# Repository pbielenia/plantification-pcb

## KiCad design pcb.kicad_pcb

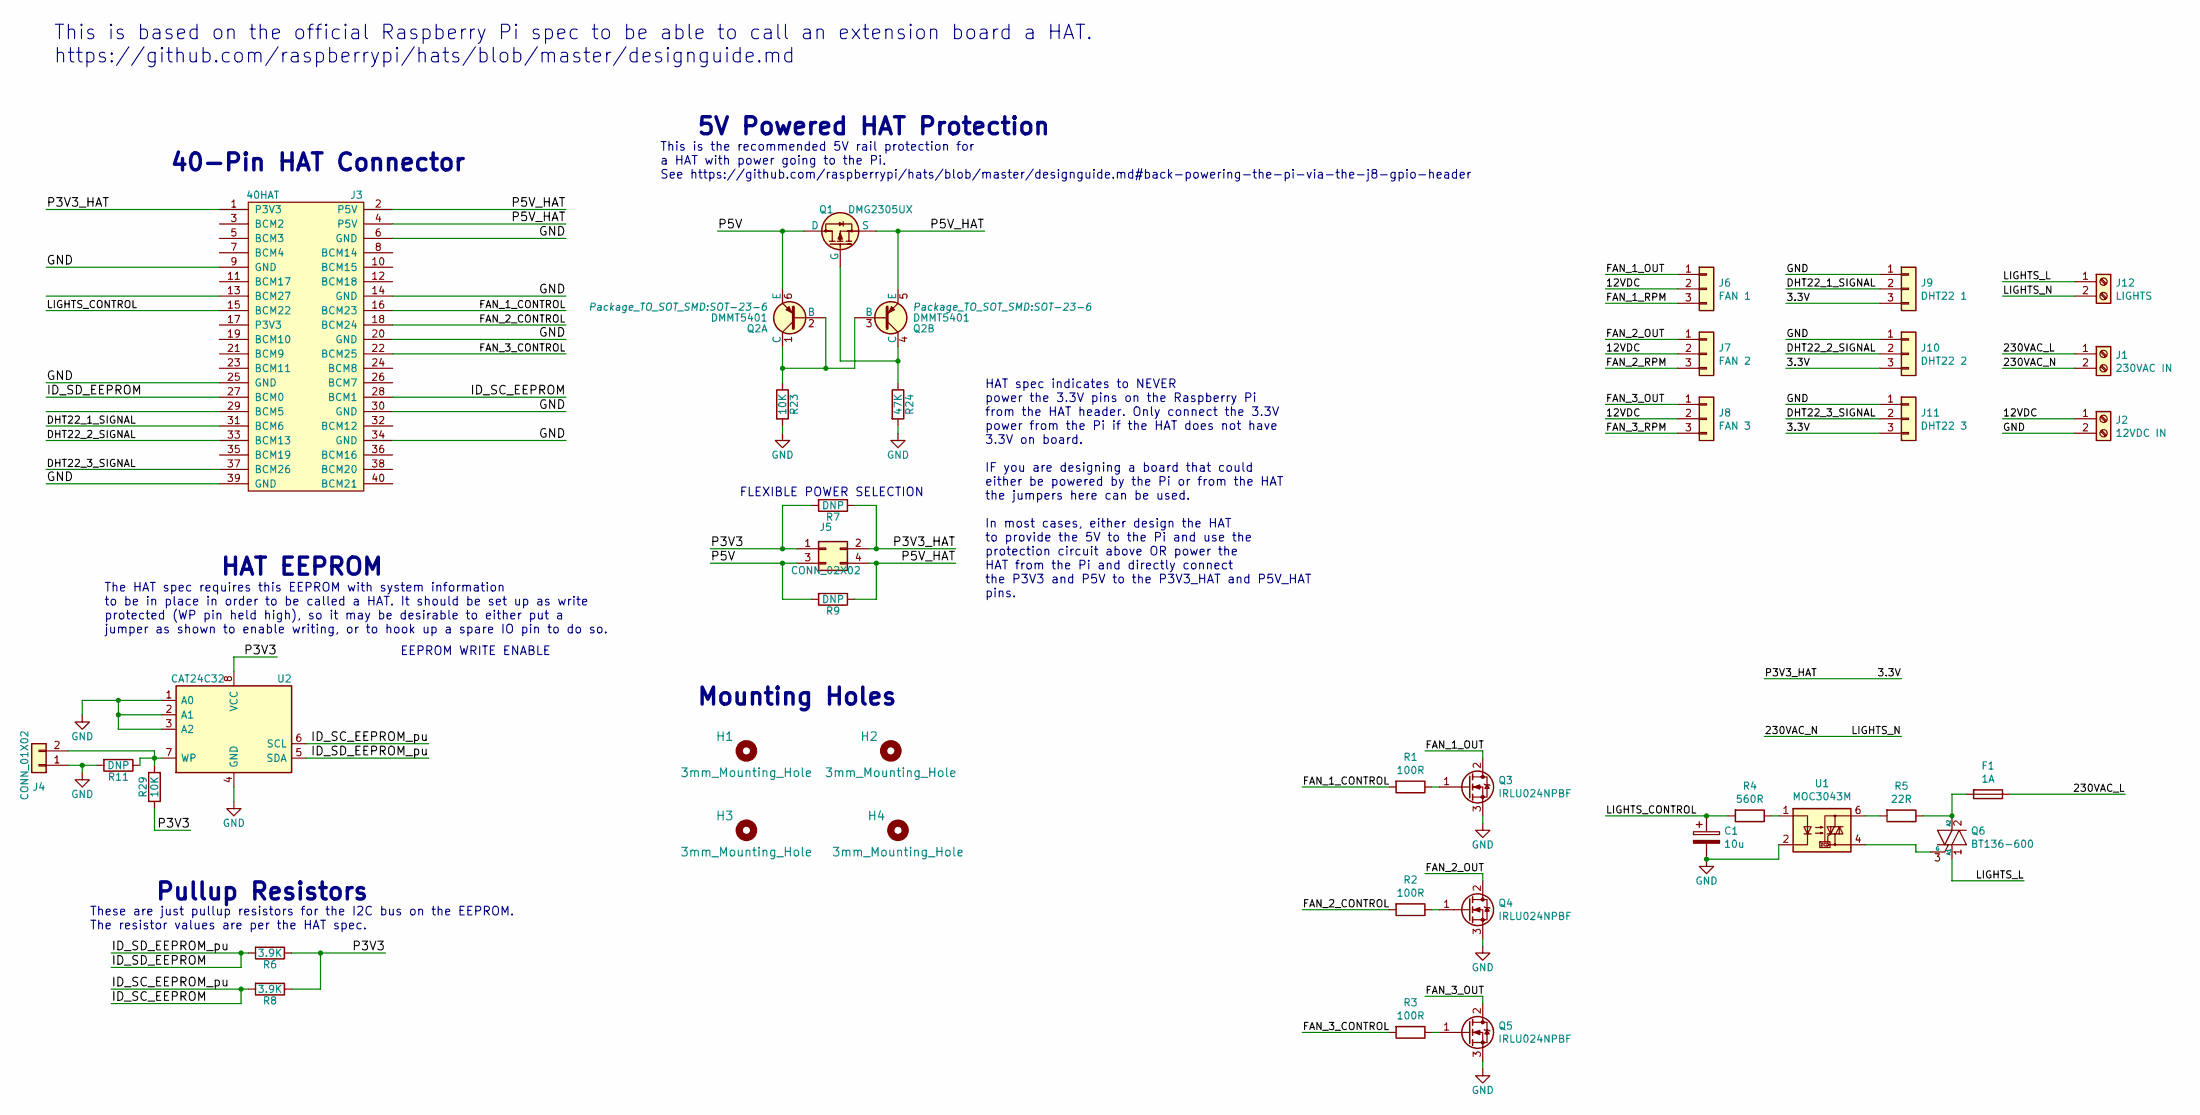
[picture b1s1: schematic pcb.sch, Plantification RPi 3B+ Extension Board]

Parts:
C1: 10u; CP_Elec_4x5.3
F1: 1A; Fuseholder_Cylinder-5x20mm_Schurter_0031_8201_Horizontal_Op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
H1, H2, H3, H4: 3mm_Mounting_Hole; NPTH_3mm_ID
J1: 230VAC IN; TerminalBlock_TE_282834-2_1x02_P2.54mm_Horizontal
J2: 12VDC IN; TerminalBlock_TE_282834-2_1x02_P2.54mm_Horizontal
J3: 40HAT; PinSocket_2x20_P2.54mm_Vertical
J4: CONN_01X02; PinHeader_1x02_P2.54mm_Vertical
J5: CONN_02X02; PinHeader_2x02_P2.54mm_Vertical
J6: FAN 1; Molex_KK-254_AE-6410-03A_1x03_P2.54mm_Vertical
J7: FAN 2; Molex_KK-254_AE-6410-03A_1x03_P2.54mm_Vertical
J8: FAN 3; Molex_KK-254_AE-6410-03A_1x03_P2.54mm_Vertical
J9: DHT22 1; Molex_KK-254_AE-6410-03A_1x03_P2.54mm_Vertical
J10: DHT22 2; Molex_KK-254_AE-6410-03A_1x03_P2.54mm_Vertical
J11: DHT22 3; Molex_KK-254_AE-6410-03A_1x03_P2.54mm_Vertical
J12: LIGHTS; TerminalBlock_TE_282834-2_1x02_P2.54mm_Horizontal
Q1: DMG2305UX; SOT-23
Q2: DMMT5401; SOT-23-6
Q3, Q4, Q5: IRLU024NPBF; TO-251-3-1EP_Horizontal_TabDown
Q6: BT136-600; TO-220-3_Horizontal_TabDown
R1, R2, R3: 100R; R_1206_3216Metric_Pad1.30x1.75mm_HandSolder
R4: 560R; R_1206_3216Metric_Pad1.30x1.75mm_HandSolder
R5: 22R; R_1206_3216Metric_Pad1.30x1.75mm_HandSolder
R6, R8: 3.9K; R_0603_1608Metric_Pad0.84x1.00mm_HandSolder
R7, R9, R11: DNP; R_0603_1608Metric_Pad0.84x1.00mm_HandSolder
R23, R29: 10K; R_0603_1608Metric_Pad0.84x1.00mm_HandSolder
R24: 47K; R_0603_1608Metric_Pad0.84x1.00mm_HandSolder
U1: MOC3043M; DIP-6_W7.62mm
U2: CAT24C32; SOIC-8_3.9x4.9mm_P1.27mm

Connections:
/3.3V: J3.1 (P3V3), J5.2, J9.3, J10.3, J11.3, R7.1
/12VDC: J2.1, J6.2, J7.2, J8.2
/230VAC_L: F1.1, J1.1
/230VAC_N: J1.2, J12.2
/DHT22_1_SIGNAL: J3.31 (BCM6), J9.2
/DHT22_2_SIGNAL: J3.33 (BCM13), J10.2
/DHT22_3_SIGNAL: J3.37 (BCM26), J11.2
/FAN_1_CONTROL: J3.16 (BCM23), R1.2
/FAN_1_OUT: J6.1, Q3.2 (D)
/FAN_1_RPM: J6.3
/FAN_2_CONTROL: J3.18 (BCM24), R2.2
/FAN_2_OUT: J7.1, Q4.2 (D)
/FAN_2_RPM: J7.3
/FAN_3_CONTROL: J3.22 (BCM25), R3.2
/FAN_3_OUT: J8.1, Q5.2 (D)
/FAN_3_RPM: J8.3
/ID_SC_EEPROM: J3.28 (BCM1), R8.2, U2.6 (SCL)
/ID_SD_EEPROM: J3.27 (BCM0), R6.2, U2.5 (SDA)
/LIGHTS_CONTROL: C1.1, J3.15 (BCM22), R4.2
/LIGHTS_L: J12.1, Q6.1 (A1)
/P3V3: J5.1, R6.1, R7.2, R8.1, R29.1, U2.8 (VCC)
/P5V: J5.3, Q1.3 (D), Q2.6 (E), R9.2
/P5V_HAT: J3.2 (P5V), J3.4 (P5V), J5.4, Q1.2 (S), Q2.5 (E), R9.1
GND: C1.2, J2.2, J3.6 (GND), J3.9 (GND), J3.14 (GND), J3.20 (GND), J3.25 (GND), J3.30 (GND), J3.34 (GND), J3.39 (GND), J4.1, J9.1, J10.1, J11.1, Q3.3 (S), Q4.3 (S), Q5.3 (S), R11.2, R23.2, R24.2, U1.2, U2.1 (A0), U2.2 (A1), U2.3 (A2), U2.4 (GND)
unnamed: F1.2, Q6.2 (A2), R5.1
unnamed: J4.2, R11.1, R29.2, U2.7 (WP)
unnamed: Q1.1 (G), Q2.4 (C), R24.1
unnamed: Q2.1 (C), Q2.2 (B), Q2.3 (B), R23.1
unnamed: Q3.1 (G), R1.1
unnamed: Q4.1 (G), R2.1
unnamed: Q5.1 (G), R3.1
unnamed: Q6.3 (G), U1.4
unnamed: R4.1, U1.1
unnamed: R5.2, U1.6

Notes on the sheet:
FLEXIBLE POWER SELECTION
5V Powered HAT Protection
This is the recommended 5V rail protection for a HAT with power going to the Pi. See https://github.com/raspberrypi/hats/blob/master/designguide.md#back-powering-the-pi-via-the-j8-gpio-header
EEPROM WRITE ENABLE
Pullup Resistors
HAT EEPROM
Mounting Holes
40-Pin HAT Connector
HAT spec indicates to NEVER power the 3.3V pins on the Raspberry Pi from the HAT header. Only connect the 3.3V power from the Pi if the HAT does not have 3.3V on board. IF you are designing a board that could either be powered by the Pi or from the HAT the jumpers here can be used. In most cases, e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
The HAT spec requires this EEPROM with system information to be in place in order to be called a HAT. It should be set up as write protected (WP pin held high), so it may be desirable to either put a jumper as shown to enable writing, or to hook up a spare IO pin to do so.
These are just pullup resistors for the I2C bus on the EEPROM. The resistor values are per the HAT spec.
This is based on the official Raspberry Pi spec to be able to call an extension board a HAT. https://github.com/raspberrypi/hats/blob/master/designguide.md

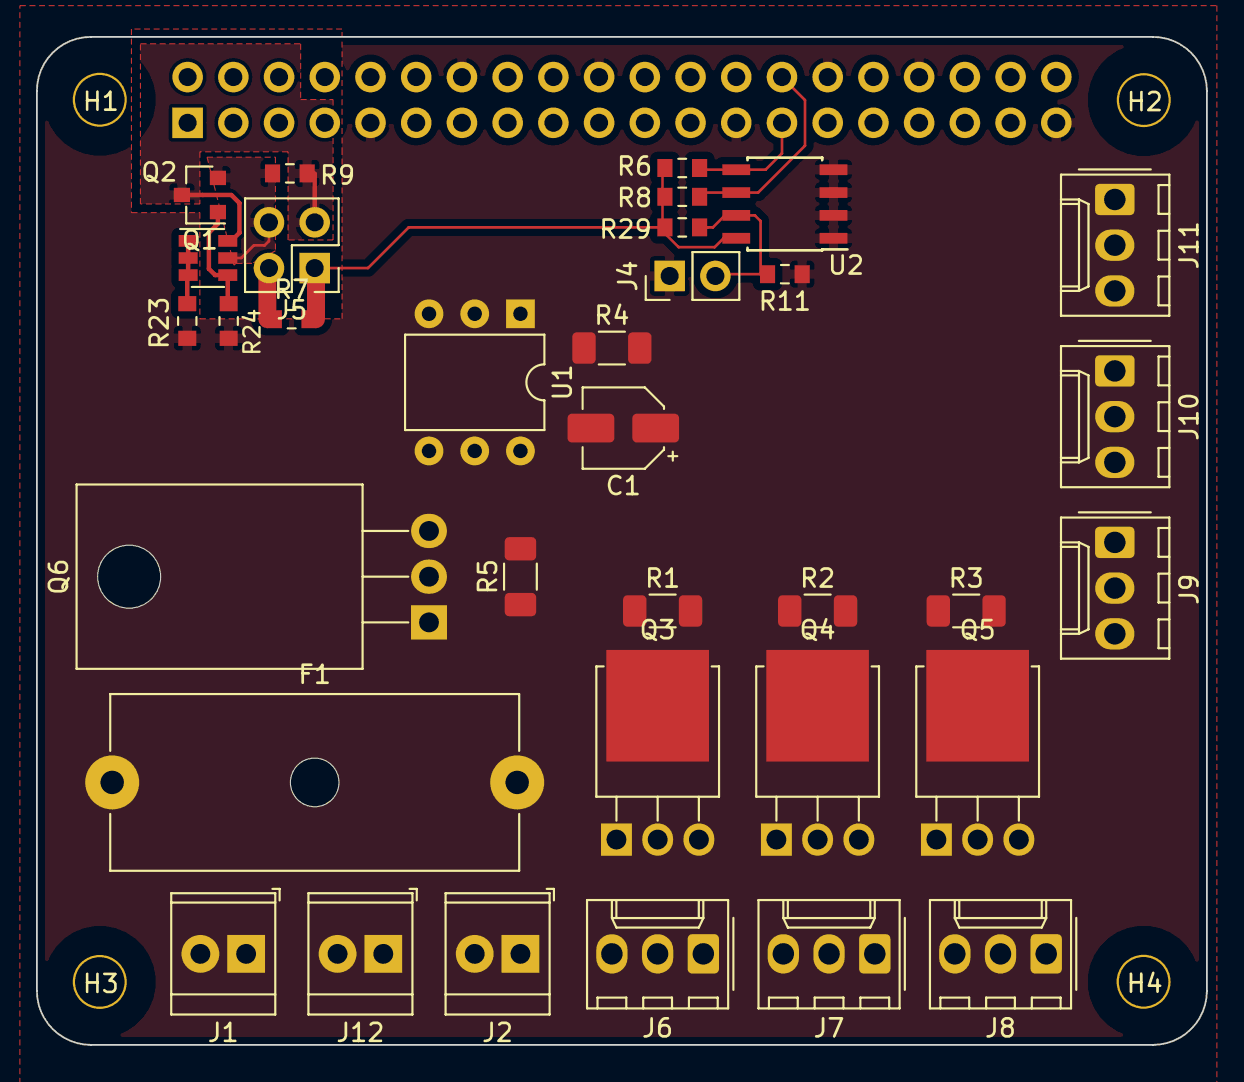
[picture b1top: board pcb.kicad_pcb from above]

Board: 4 copper layers, 65.0 x 56.0 mm, 39 parts (1 on the bottom side), 31 nets.

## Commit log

2020-11-28 Create gitignore
2020-11-28 Add fans, dht22 and RPi hat
2020-12-05 Rearranged connectors. Added early triac circuit.
2020-12-05 Set optoisolator and triac footprints
2020-12-05 Remove fan speed connectors
2020-12-05 Connect devices to the RPi connector
2020-12-05 Connect devices 3.3V to HAT's 3.3V
